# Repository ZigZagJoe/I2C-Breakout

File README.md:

<h3>Breakout board w/  I2C controller PCA9665</h3> 
<br>
<br><a href="https://oshpark.com/profiles/ZigZagJoe"><br>Order PCB here!</a><br><br><b>Features:</b><br>
100khz to 1mhz I2C bus<br>
5V-tolerant I/O<br>
3.3v VCC<br>
68 byte buffer<br><br>
30 pins (2x15),  0.1" spacing,  0.6" pin width<br>2 layer, 1.55" x 0.76" (39.37x19.20 mm)<br>

<h4>Optional parts:</h4>
<b>3.3v regulator MCP1700</b>, 3.5v-6v Vin, 250ma<br>

<b>I2C-SPI bridge SC18IS602</b><br>
<b>I2C ADC MCP3221A</b>, 1ch, 12bit<br>
<b>I2C EEPROM</b>, SOT23-5<br>
<b>OC driver for /CS -> /DTACK</b><br>

<br><b>Changelog</b><br>
<b>Rev2:</b> Fixed ADC layout (transposed Vcc and Gnd)</br>

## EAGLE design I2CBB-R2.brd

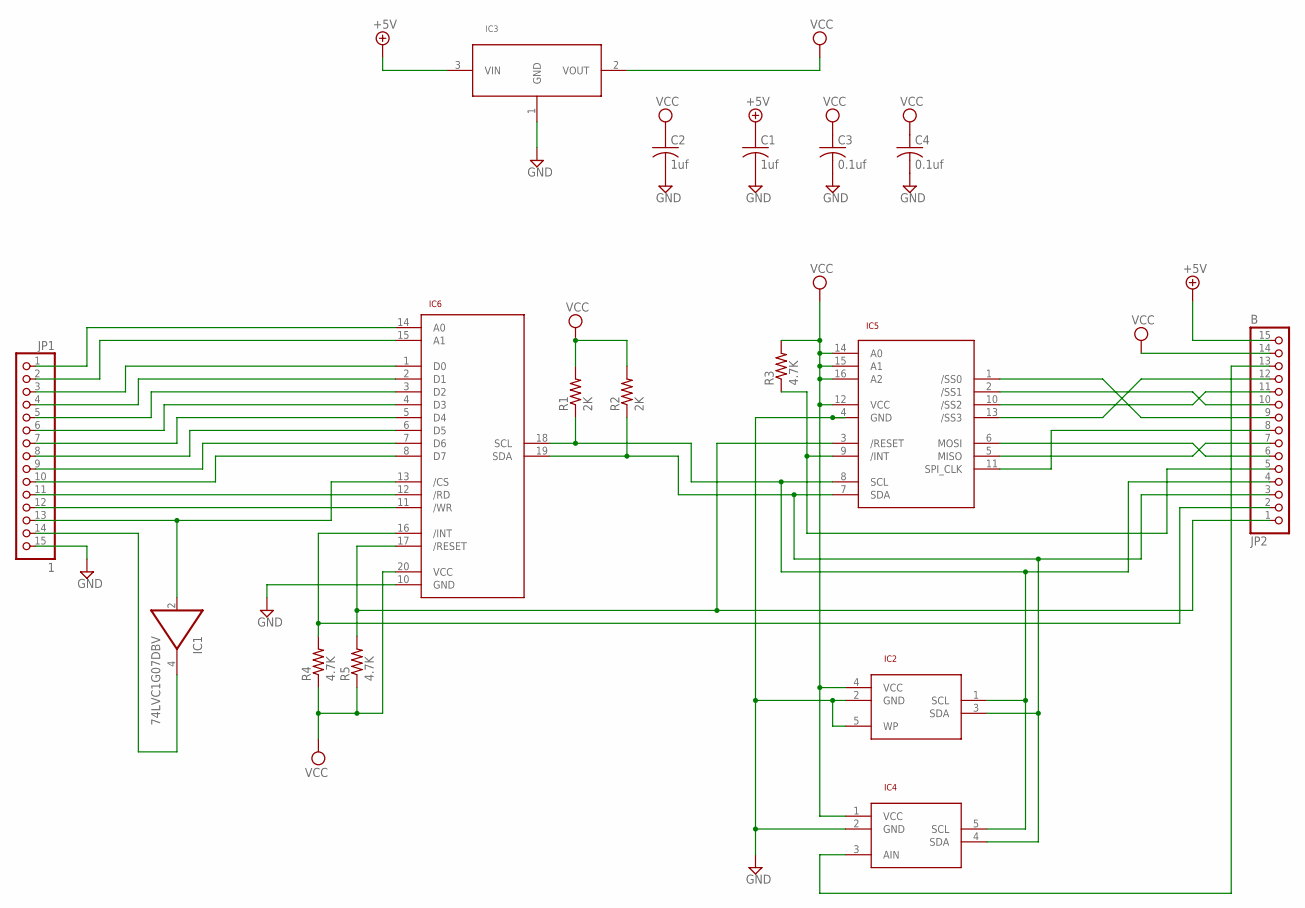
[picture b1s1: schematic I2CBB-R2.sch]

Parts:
C1, C2: 1uf; C0603
C3, C4: 0.1uf; C0603
IC1: 74LVC1G07DBV; SOT23-5
IC2: 24AA64T; SOT23-5
IC3: MCP1700T; SOT23
IC4: MCP3221; SOT23-5
IC5: SC18IS602; TSSOP16
IC6: PCA9665; TSSOP20
JP1: 1; 1X15
JP2: B; 1X15
R1, R2: 2K; R0603
R3, R4, R5: 4.7K; R0603

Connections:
+5V: C1.1, IC3.3 (VIN), JP2.15
/INTI2C: IC6.16 (/INT), JP2.2, R4.2
AIN: IC4.3 (AIN), JP2.13
GND: C1.2, C2.2, C3.2, C4.2, IC1.3 (GND), IC2.2 (GND), IC2.5 (WP), IC3.1 (GND), IC4.2 (GND), IC5.4 (GND), IC6.10 (GND), JP1.15
unnamed: IC1.2 (I), IC6.13 (/CS), JP1.13
unnamed: IC1.4 (O), JP1.14
unnamed: IC6.11 (/WR), JP1.12
unnamed: IC6.12 (/RD), JP1.11
unnamed: IC6.14 (A0), JP1.1
unnamed: IC6.15 (A1), JP1.2
unnamed: IC6.1 (D0), JP1.3
unnamed: IC6.2 (D1), JP1.4
unnamed: IC6.3 (D2), JP1.5
unnamed: IC6.4 (D3), JP1.6
unnamed: IC6.5 (D4), JP1.7
unnamed: IC6.6 (D5), JP1.8
unnamed: IC6.7 (D6), JP1.9
unnamed: IC6.8 (D7), JP1.10
unnamed: IC5.9 (/INT), JP2.5, R3.1
unnamed: IC5.10 (/SS2), JP2.11
unnamed: IC5.2 (/SS1), JP2.10
unnamed: IC5.1 (/SS0), JP2.9
unnamed: IC5.13 (/SS3), JP2.12
unnamed: IC5.5 (MISO), JP2.7
unnamed: IC5.6 (MOSI), JP2.6
unnamed: IC5.11 (SPI_CLK), JP2.8
RESET: IC5.3 (/RESET), IC6.17 (/RESET), JP2.1, R5.2
SCL: IC2.1 (SCL), IC4.5 (SCL), IC5.8 (SCL), IC6.18 (SCL), JP2.4, R1.1
SDA: IC2.3 (SDA), IC4.4 (SDA), IC5.7 (SDA), IC6.19 (SDA), JP2.3, R2.1
VCC: C2.1, C3.1, C4.1, IC1.5 (VCC), IC2.4 (VCC), IC3.2 (VOUT), IC4.1 (VCC), IC5.12 (VCC), IC5.14 (A0), IC5.15 (A1), IC5.16 (A2), IC6.20 (VCC), JP2.14, R1.2, R2.2, R3.2, R4.1, R5.1

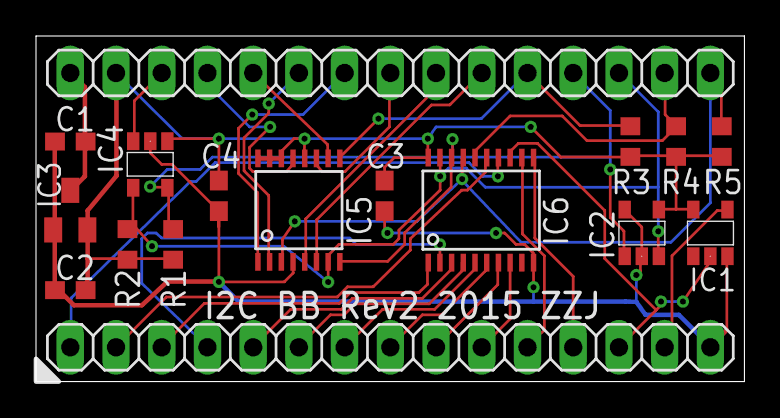
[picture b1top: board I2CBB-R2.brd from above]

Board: 2 copper layers, 39.4 x 19.2 mm, 17 parts (0 on the bottom side), 30 nets.

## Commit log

2015-06-22 Add OSHPARK link to order PCBs
2015-06-27 Fix MCP3221 layout - transposed GND and Vcc
2015-06-27 Add rev2 - fix transposed vcc and gnd on MCP3221
2015-06-30 Better trace routing on ADC
2015-06-30 Add borders and class to pinout, and add picture
2015-06-30 Updated with picture and R2 info
2015-06-30 Add R2 simulated pictures
